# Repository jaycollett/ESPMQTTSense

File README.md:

# ESPMQTTSense
ESP8266 based environment sensor using the BME280 and MQTT communication. Designed to populate sensor data in my HASS.IO system. More details can be found in my blog post about this project [here](https://www.jaycollett.com/2018/03/cheap-environment-sensing-with-esp8266-mqtt).

**BOM**
----------
1. [ESP8266 ESP-01](https://www.aliexpress.com/item/WiFi-module-ESP8266-Serial-to-WiFi-wireless-transparent-transmission-industrial-ESP-01S/32716268094.html)
2. [Custom OSH Park PCBs x 3](https://oshpark.com/shared_projects/DTD2a0g7)
3. Passive Components - micro usb is part number: 10103594-0001LF
4. [Enclosure x5](https://www.ebay.com/itm/H1-5pcs-Plastic-Electric-Project-Junction-Box-60x36x25mm/282124733873)
5. [BME280 Sensor Module](https://www.banggood.com/CJMCU-280E-BME280-High-Precision-Atmospheric-Pressure-Sensor-For-Arduino-p-1103115.html)
6. [USB Wall Plug](https://www.aliexpress.com/item/Universal-USB-Charger-US-EU-Plug-5V-1A-Charger-Adapter-for-iphone-6-6s-7-7s/32822757190.html)
7. [1m USB Micro Cable](https://www.aliexpress.com/item/USB-Cable-Micro-USB-Cable-Charging-Sync-Data-Mobile-Phone-Cables-For-Android-Samsung-Xiaomi-Huawei/32852902325.html)

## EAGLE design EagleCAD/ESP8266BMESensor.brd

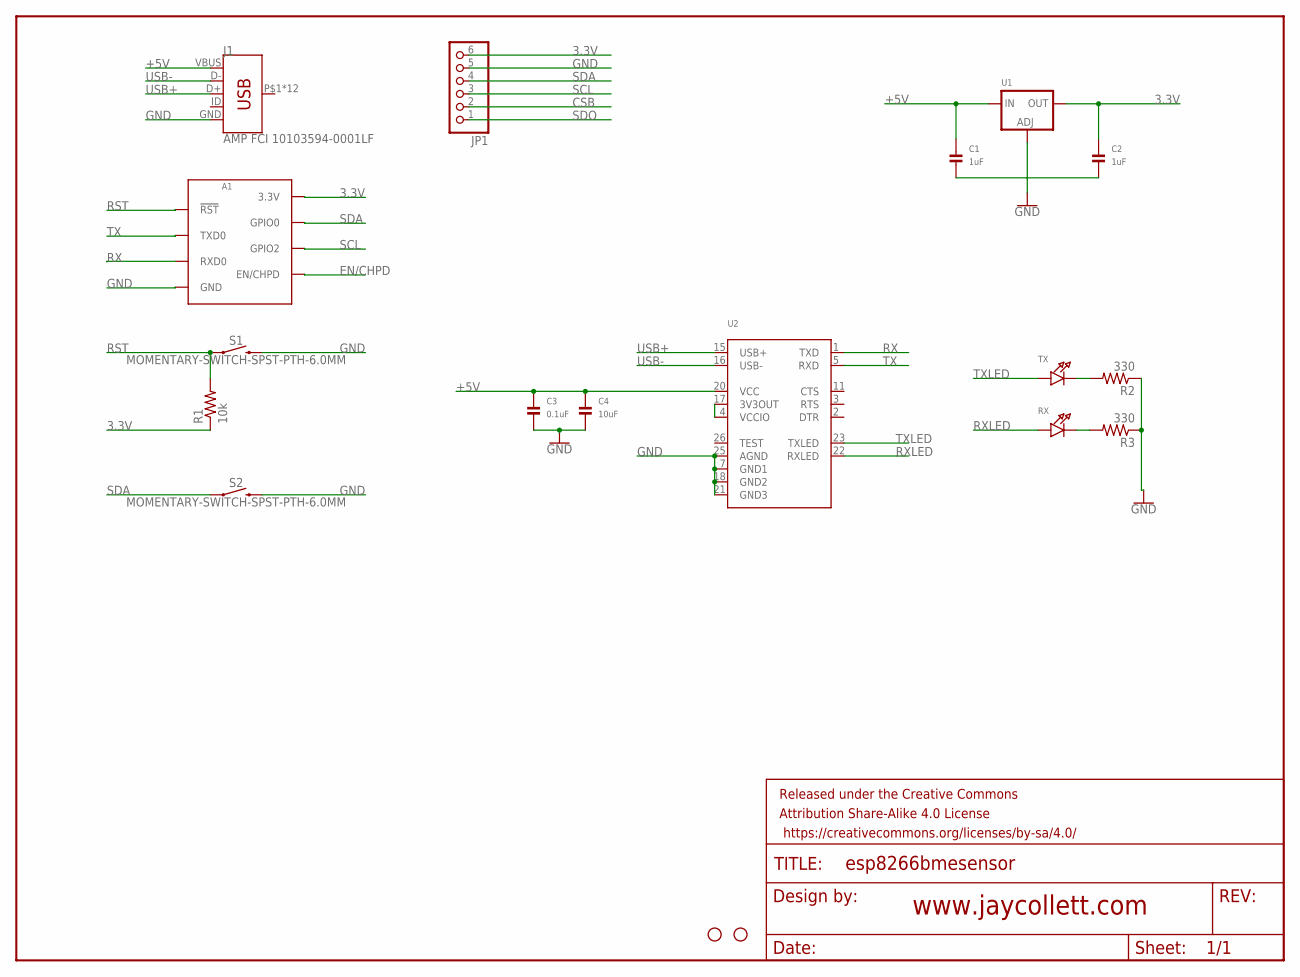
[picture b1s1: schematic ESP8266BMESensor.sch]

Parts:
A1: ESP8266_ESP-01; ESP8266_ESP-01_NO-SILKSCREEN
C1, C2: 1uF; 0805
C3: 0.1uF; 0805
C4: 10uF; 0805
FRAME1: FRAME-LETTERNO_PACKAGE; DUMMY
H2, H4: STAND-OFF
J1: AMP FCI 10103594-0001LF; USB-MICROB-PTH
JP1: PINHD-1X6CB; 1X06-CLEANBIG
R1: 10k; R0805
R2, R3: 330; R0805
RX: LED0805_NOOUTLINE; CHIPLED_0805_NOOUTLINE
S1, S2: MOMENTARY-SWITCH-SPST-PTH-6.0MM; TACTILE_SWITCH_PTH_6.0MM
TX: LED0805_NOOUTLINE; CHIPLED_0805_NOOUTLINE
U1: LM1117SOT223-WAVE; SOT223-W
U2: FT232RLSSOP28; SSOP28DB

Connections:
3.3V: A1.3V3 (3.3V), C2.1, JP1.6, R1.1, U1.2 (OUT)
+5V: C1.1, C3.1, C4.1, J1.VBUS, U1.3 (IN), U2.20 (VCC)
CSB: JP1.2
EN/CHPD: A1.EN/CH_PD (EN/CHPD)
GND: A1.GND, C1.2, C2.2, C3.2, C4.2, J1.GND, JP1.5, R2.1, R3.1, S1.3 (2), S2.3 (2), U1.1 (ADJ), U2.7 (GND1), U2.18 (GND2), U2.21 (GND3), U2.25 (AGND)
unnamed: R2.2, TX.C
unnamed: R3.2, RX.C
RST: A1.RST (!RST!), R1.2, S1.1
RX: A1.RX (RXD0), U2.1 (TXD)
RXLED: RX.A, U2.22 (RXLED)
SCL: A1.GPIO2, JP1.3
SDA: A1.GPIO0, JP1.4, S2.1
SDO: JP1.1
TX: A1.TX (TXD0), U2.5 (RXD)
TXLED: TX.A, U2.23 (TXLED)
USB+: J1.D+, U2.15 (USB+)
USB-: J1.D-, U2.16 (USB-)
VCCIO: U2.4 (VCCIO), U2.17 (3V3OUT)

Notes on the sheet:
www.jaycollett.com

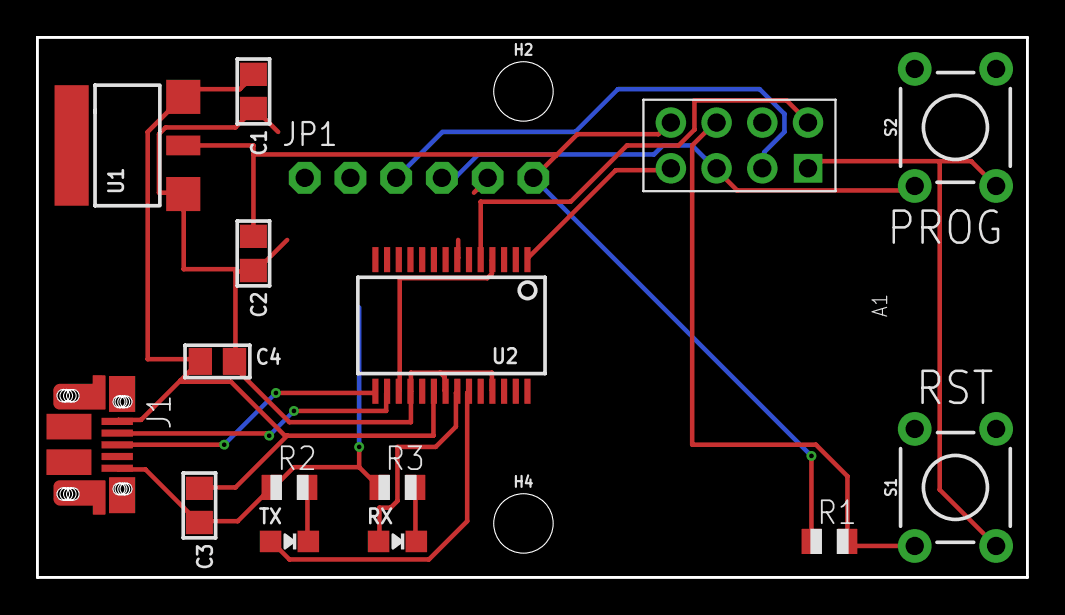
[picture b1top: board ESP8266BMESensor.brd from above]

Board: 2 copper layers, 55.0 x 30.0 mm, 19 parts (0 on the bottom side), 15 nets.

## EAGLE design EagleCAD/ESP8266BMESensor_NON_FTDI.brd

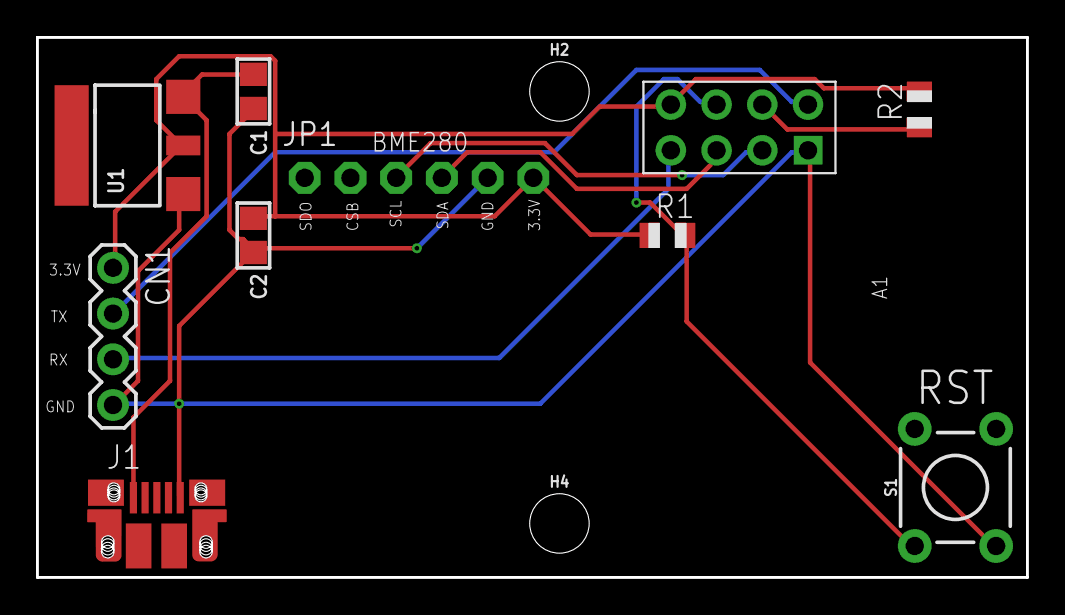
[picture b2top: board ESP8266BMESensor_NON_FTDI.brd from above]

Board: 2 copper layers, 55.0 x 30.0 mm, 13 parts (0 on the bottom side), 9 nets.

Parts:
A1: ESP8266_ESP-01_NO-SILKSCREEN
C1, C2: 1uF; 0805
CN1: 1X4-BIG; 1X04-BIG
FRAME1: FRAME-LETTERNO_PACKAGE; DUMMY
H2, H4: STAND-OFF
J1: AMP FCI 10103594-0001LF; USB-MICROB-PTH
JP1: 1X06-CLEANBIG
R1: 10k; R0805
R2: R0805
S1: MOMENTARY-SWITCH-SPST-PTH-6.0MM; TACTILE_SWITCH_PTH_6.0MM
U1: SOT223-W

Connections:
3.3V: A1.3V3, C2.1, CN1.1, JP1.6, R1.1, R2.2, U1.2
+5V: C1.1, J1.VBUS, U1.3
EN/CHPD: A1.EN/CH_PD, R2.1
GND: A1.GND, C1.2, C2.2, CN1.4, J1.GND, JP1.5, S1.3, U1.1
RST: A1.RST, R1.2, S1.1
RX: A1.RX, CN1.3
SCL: A1.GPIO2, JP1.3
SDA: A1.GPIO0, JP1.4
TX: A1.TX, CN1.2

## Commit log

2018-03-01 inital commit
2018-03-01 fixing directory structure for project
2018-03-01 adding arduino code
2018-03-01 fixing up mqtt topics
2018-03-03 updating PCB and adding USB to UART IC
2018-03-04 initial version of firmware
2018-03-06 adding eagle png files
2018-03-17 fixing pinout for scl sda
2018-03-17 fixinng SDA/SCL pins and setting MQTT update to 5 mins
2018-03-17 adding 3d printed folders
2018-03-20 adding travis file for auto builds
2018-03-20 adding travis build badge and license badge
2018-03-20 updating url for badges
2018-03-25 adding back the FTDI version as the primary
2018-03-25 updating oshpark link for board v1.4
2018-03-26 fixing mqtt clientID parameter
2018-03-26 updating decimal places for values, add fmver topic
2018-03-26 updating to include blog url for more info.
2018-04-02 fixing bug with IP printing
2022-04-21 New version which includes the WiFiManager AP to ease initial and reset of WiFi
2024-01-28 Updates firmware to publish on start-up and bumps lib versions

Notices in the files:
parts and their libraries:
microbuilder: This work is placed in the public domain, and may be freely used for commercial and non-commercial work with the following conditions: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
SparkFun-Aesthetics: Licensing: Creative Commons ShareAlike 4.0 International - https://creativecommons.org/licenses/by-sa/4.0
